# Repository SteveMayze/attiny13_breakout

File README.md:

# ATTiny13 Breakout and Development board

This project defines a small PCB to take an ATTiny13, and a 3.3V LDO. Power can be supplied by a USB Micro connector or 5V applied directly to the board. All GPIO are broken out as is the 3.3V and the input 5V.

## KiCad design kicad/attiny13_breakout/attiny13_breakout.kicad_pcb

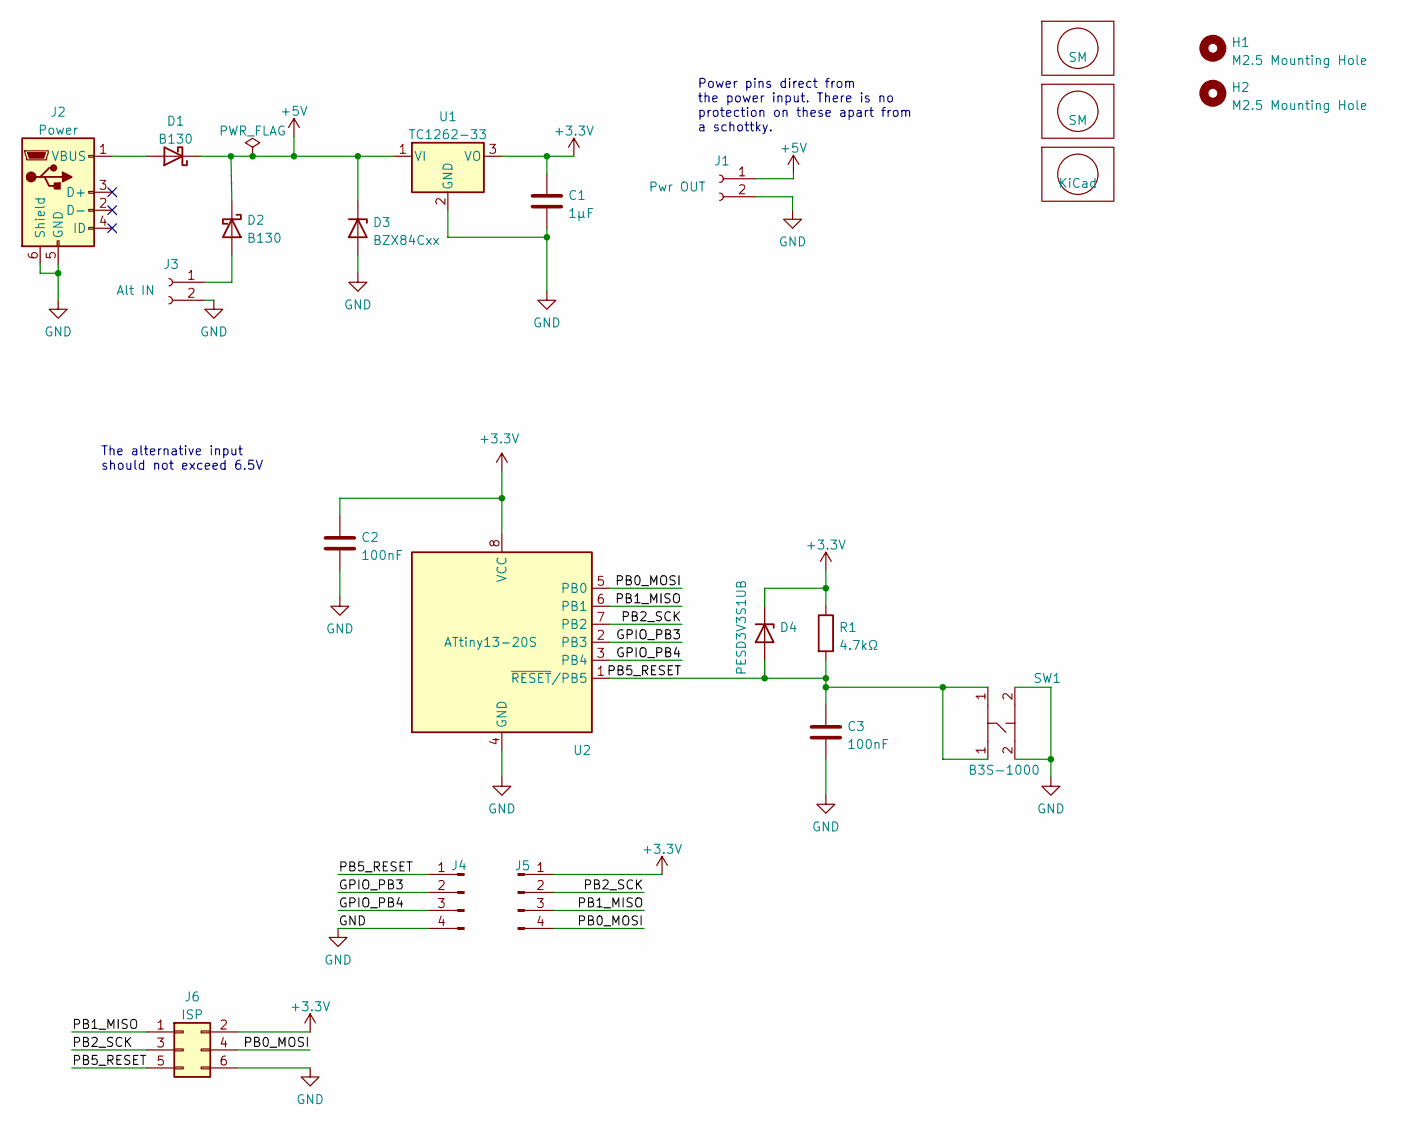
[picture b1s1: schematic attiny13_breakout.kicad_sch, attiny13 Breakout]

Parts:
C1: 1μF; C_0805_2012Metric_Pad1.18x1.45mm_HandSolder
C2, C3: 100nF; C_0805_2012Metric_Pad1.18x1.45mm_HandSolder
D1, D2: B130; D_SMA
D3: BZX84Cxx; SOT-23
D4: PESD3V3S1UB; D_SOD-523
H1, H2: M2.5 Mounting Hole; MountingHole_2.7mm_M2.5
J1: Pwr OUT; PinHeader_1x02_P2.54mm_Vertical
J2: Power; USB_Micro-B_Amphenol_10103594-0001LF_Horizontal
J3: Alt IN; PinHeader_1x02_P2.54mm_Vertical
J4, J5: Conn_01x04_Male; PinHeader_1x04_P2.54mm_Vertical
J6: ISP; Tag-Connect_TC2030-IDC-FP_2x03_P1.27mm_Vertical
Lg1, Lg3: SM; MyBasic_rounded_50_1
Lg2: KiCad; KiCad-Logo2_5mm_SilkScreen
R1: 4.7kΩ; R_0805_2012Metric_Pad1.20x1.40mm_HandSolder
SW1: B3S-1000; SW_SPST_Omron_B3FS-100xP
U1: TC1262-33; SOT-223-3_TabPin2
U2: ATtiny13-20S; SOIC-8W_5.3x5.3mm_P1.27mm

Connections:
+3.3V: C1.1, C2.1, D4.1 (K), J5.1, J6.2, R1.1, U1.3 (VO), U2.8 (VCC)
+5V: D1.1 (K), D2.1 (K), D3.3 (K), J1.1, U1.1 (VI)
/GPIO_PB3: J4.2, U2.2 (PB3)
/GPIO_PB4: J4.3, U2.3 (PB4)
/PB0_MOSI: J5.4, J6.4, U2.5 (PB0)
/PB1_MISO: J5.3, J6.1, U2.6 (PB1)
/PB2_SCK: J5.2, J6.3, U2.7 (PB2)
/PB5_RESET: C3.1, D4.2 (A), J4.1, J6.5, R1.2, SW1.1, U2.1 (~RESET/PB5)
GND: C1.2, C2.2, C3.2, D3.1 (A), J1.2, J2.5 (GND), J2.6 (Shield), J3.2, J4.4, J6.6, SW1.2, U1.2 (GND), U2.4 (GND)
unnamed: D1.2 (A), J2.1 (VBUS)
unnamed: D2.2 (A), J3.1

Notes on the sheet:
Power pins direct from the power input. There is no protection on these apart from a schottky.
The alternative input should not exceed 6.5V

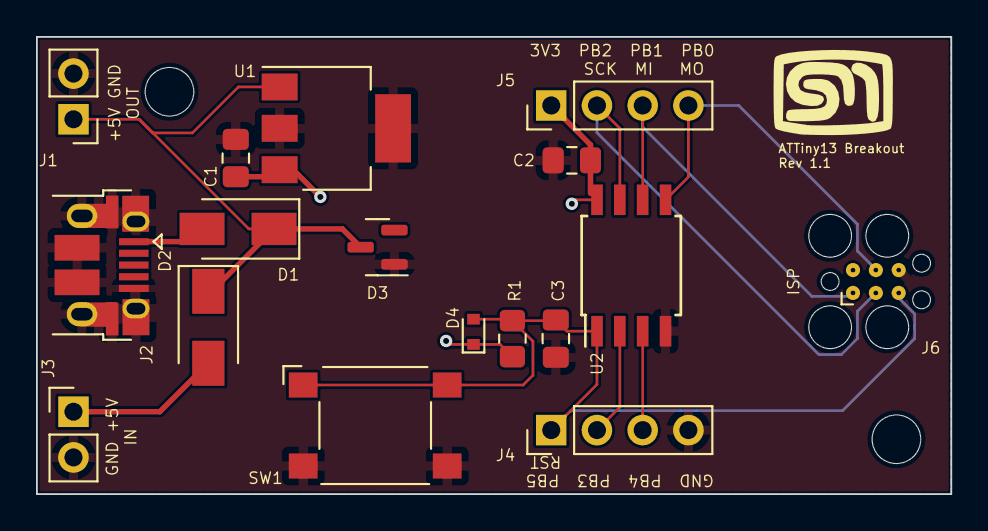
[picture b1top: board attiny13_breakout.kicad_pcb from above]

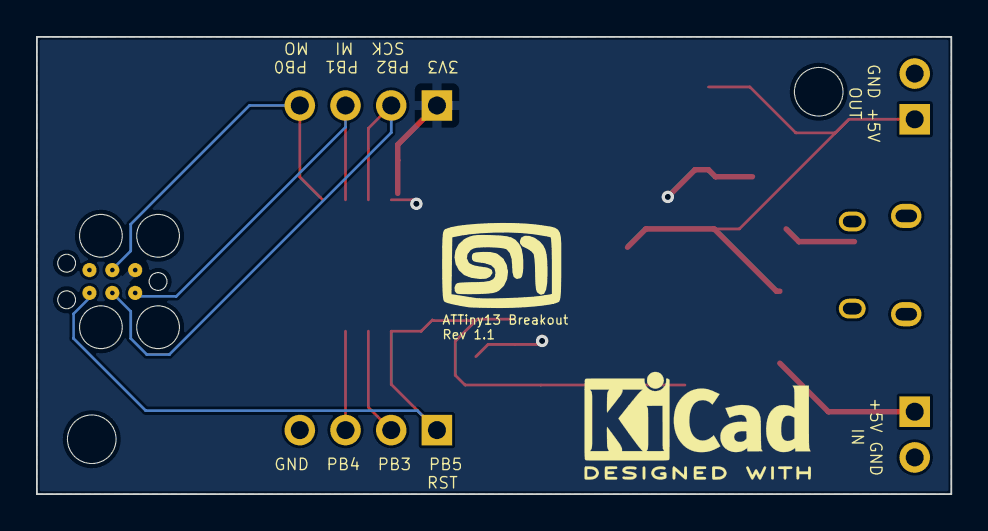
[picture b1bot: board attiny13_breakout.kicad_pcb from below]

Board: 2 copper layers, 50.8 x 25.4 mm, 22 parts (2 on the bottom side), 11 nets.

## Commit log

2022-12-20 Create .gitignore for KiCad
2022-12-20 Design and layout
2022-12-20 Adds the schematic as a PDF for reference
2022-12-20 secure some backups
2023-01-15 Net correction for Rev 1.1
2023-01-15 Update the revision
2023-01-21 Metadata update
2023-01-21 Path and library reference corrections
